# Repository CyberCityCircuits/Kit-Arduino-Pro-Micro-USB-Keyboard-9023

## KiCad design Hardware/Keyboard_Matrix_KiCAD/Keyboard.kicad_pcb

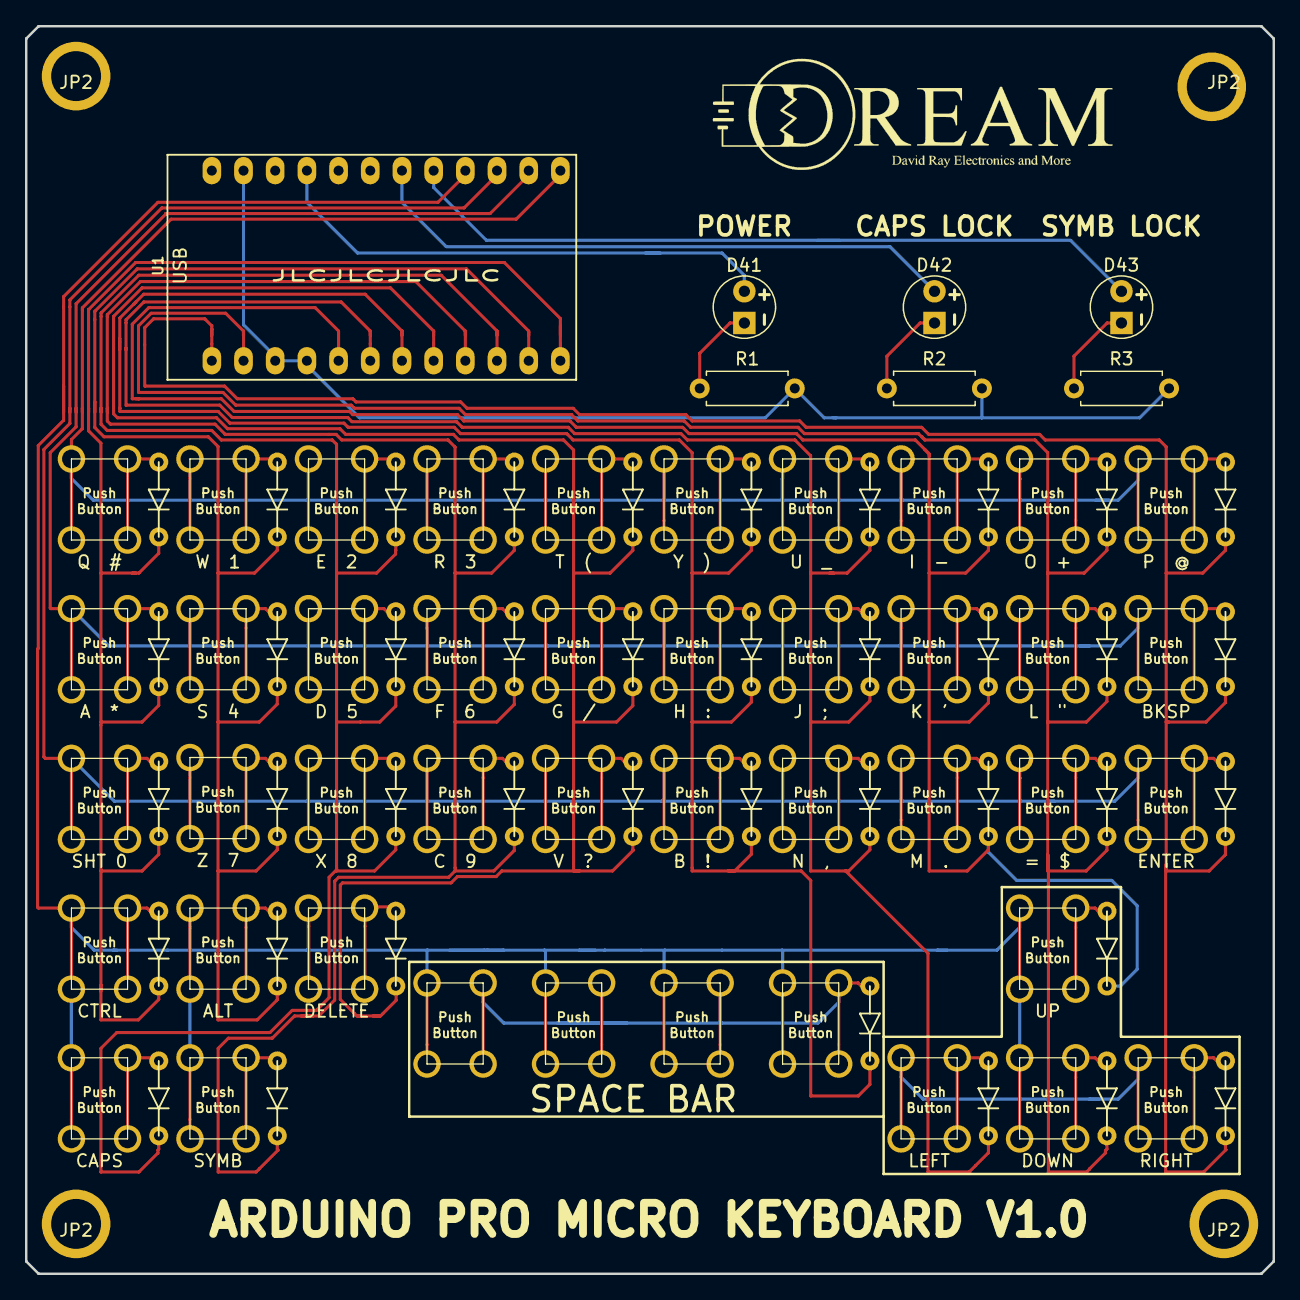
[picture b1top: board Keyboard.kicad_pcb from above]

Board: 2 copper layers, 100.0 x 100.0 mm, 94 parts (0 on the bottom side), 61 nets.

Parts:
=  $: SW_Push; Kailanda Push Button 6.5x4.5_002
A  *: SW_Push; Kailanda Push Button 6.5x4.5_002
ALT: SW_Push; Kailanda Push Button 6.5x4.5_002
B  !: SW_Push; Kailanda Push Button 6.5x4.5_002
BKSP: SW_Push; Kailanda Push Button 6.5x4.5_002
C  9: SW_Push; Kailanda Push Button 6.5x4.5_002
CAPS: SW_Push; Kailanda Push Button 6.5x4.5_002
CTRL: SW_Push; Kailanda Push Button 6.5x4.5_002
D1, D2, D3, D4, D5, D6, D7, D8, D9, D10, D11, D12, D13, D14, D15, D16, D17, D18, D19, D20, D21, D22, D23, D24, D25, D26, D27, D28, D29, D30, D31, D32, D33, D34, D35, D36, D37, D38, D39, D40: 1N4148; DIODE_P6_03kicad_mod
D41, D42, D43: LED; LED_D5.0mm_05
D  5: SW_Push; Kailanda Push Button 6.5x4.5_002
DELETE: SW_Push; Kailanda Push Button 6.5x4.5_002
DOWN: SW_Push; Kailanda Push Button 6.5x4.5_002
E  2: SW_Push; Kailanda Push Button 6.5x4.5_002
ENTER: SW_Push; Kailanda Push Button 6.5x4.5_002
F  6: SW_Push; Kailanda Push Button 6.5x4.5_002
G  /: SW_Push; Kailanda Push Button 6.5x4.5_002
H  :: SW_Push; Kailanda Push Button 6.5x4.5_002
I  -: SW_Push; Kailanda Push Button 6.5x4.5_002
J  ;: SW_Push; Kailanda Push Button 6.5x4.5_002
JP2, JP2#2, JP2#3, JP2#4: 2mm_Hole; 4mm_Mount_Hole
K  ': SW_Push; Kailanda Push Button 6.5x4.5_002
L  ": SW_Push; Kailanda Push Button 6.5x4.5_002
LEFT: SW_Push; Kailanda Push Button 6.5x4.5_002
M  .: SW_Push; Kailanda Push Button 6.5x4.5_002
N  ,: SW_Push; Kailanda Push Button 6.5x4.5_002
O  +: SW_Push; Kailanda Push Button 6.5x4.5_002
P  @: SW_Push; Kailanda Push Button 6.5x4.5_002
Q  #: SW_Push; Kailanda Push Button 6.5x4.5_002
R1, R2, R3: 1000; R_Axial_DIN0207_L6.3mm_D2.5mm_P7.62mm_Horizontal
R  3: SW_Push; Kailanda Push Button 6.5x4.5_002
RIGHT: SW_Push; Kailanda Push Button 6.5x4.5_002
S  4: SW_Push; Kailanda Push Button 6.5x4.5_002
SHT 0: SW_Push; Kailanda Push Button 6.5x4.5_002
SPACE: SW_Push; Kailanda Push Button 6.5x4.5_002
SPACE#2, SPACE#3, SPACE#4: SW_Push; Kailanda Push Button 6.5x4.5_002
SYMB: SW_Push; Kailanda Push Button 6.5x4.5_002
T  (: SW_Push; Kailanda Push Button 6.5x4.5_002
U1: ArduinoProMicro; Arduino_Pro_Micro
U  _: SW_Push; Kailanda Push Button 6.5x4.5_002
UP: SW_Push; Kailanda Push Button 6.5x4.5_002
V  ?: SW_Push; Kailanda Push Button 6.5x4.5_002
W  1: SW_Push; Kailanda Push Button 6.5x4.5_002
X  8: SW_Push; Kailanda Push Button 6.5x4.5_002
Y  ): SW_Push; Kailanda Push Button 6.5x4.5_002
Z  7: SW_Push; Kailanda Push Button 6.5x4.5_002

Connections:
A0: D43.2, U1.17
A1: D42.2, U1.18
COL1: D1.K, D11.K, D21.K, D31.K, U1.12
COL2: D2.K, D12.K, D22.K, D32.K, U1.11
COL3: D3.K, D13.K, D23.K, D33.K, U1.10
COL4: D4.K, D14.K, D24.K, D34.K, U1.9
COL5: D5.K, D15.K, D25.K, D35.K, U1.8
COL6: D6.K, D16.K, D26.K, D36.K, U1.7
COL7: D7.K, D17.K, D27.K, D37.K, U1.6
COL8: D8.K, D18.K, D28.K, D38.K, U1.5
COL9: D9.K, D19.K, D29.K, D39.K, U1.2
COL10: D10.K, D20.K, D30.K, D40.K, U1.1
GND: R1.2, R2.2, R3.2, U1.3, U1.4, U1.23
unnamed: D1.A, Q #.2
unnamed: D2.A, W 1.2
unnamed: D3.A, E 2.2
unnamed: D4.A, R 3.2
unnamed: D5.A, T (.2
unnamed: D6.A, Y ).2
unnamed: D7.A, U _.2
unnamed: D8.A, I -.2
unnamed: D9.A, O +.2
unnamed: D10.A, P @.2
unnamed: A *.2, D11.A
unnamed: D12.A, S 4.2
unnamed: D13.A, D 5.2
unnamed: D14.A, F 6.2
unnamed: D15.A, G /.2
unnamed: D16.A, H :.2
unnamed: D17.A, J ;.2
unnamed: D18.A, K '.2
unnamed: D19.A, L ".2
unnamed: BKSP.2, D20.A
unnamed: D21.A, SHT 0.2
unnamed: D22.A, Z 7.2
unnamed: D23.A, X 8.2
unnamed: C 9.2, D24.A
unnamed: D25.A, V ?.2
unnamed: B !.2, D26.A
unnamed: D27.A, N ,.2
unnamed: D28.A, M ..2
unnamed: = $.2, D29.A
unnamed: D30.A, ENTER.2
unnamed: CTRL.2, D31.A
unnamed: ALT.2, D32.A
unnamed: CAPS.2, D33.A
unnamed: D34.A, SYMB.2
unnamed: D35.A, DELETE.2
unnamed: D36.A, SPACE.2, SPACE#2.2, SPACE#3.2, SPACE#4.2
unnamed: D37.A, LEFT.2
unnamed: D38.A, UP.2
unnamed: D39.A, DOWN.2
unnamed: D40.A, RIGHT.2
unnamed: D41.1, R1.1
unnamed: D42.1, R2.1
unnamed: D43.1, R3.1
POWER: D41.2, U1.21
ROW1: E 2.1, I -.1, O +.1, P @.1, Q #.1, R 3.1, T (.1, U1.13, U _.1, W 1.1, Y ).1
ROW2: A *.1, BKSP.1, D 5.1, F 6.1, G /.1, H :.1, J ;.1, K '.1, L ".1, S 4.1, U1.14
ROW3: = $.1, B !.1, C 9.1, ENTER.1, M ..1, N ,.1, SHT 0.1, U1.15, V ?.1, X 8.1, Z 7.1
ROW4: ALT.1, CAPS.1, CTRL.1, DELETE.1, DOWN.1, LEFT.1, RIGHT.1, SPACE.1, SPACE#2.1, SPACE#3.1, SPACE#4.1, SYMB.1, U1.16, UP.1

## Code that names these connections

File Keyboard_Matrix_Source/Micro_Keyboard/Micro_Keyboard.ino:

//****************************************************
//This is for the Keyboard Matrix for sale
//on Tindie.com from David Ray Electronics and More.
//This is built around the Arduino Pro Micro.
//Use this any way you see fit.
//www.DREAM-Enterprise.com
//****************************************************

#include <Keypad.h>
#include <Keyboard.h>

int CAPS_LED = 19;
int SYMB_LED = 18;

int CAPSLOCK = 0;
int SYMBLOCK = 0;

const byte ROWS = 4;
const byte COLS = 10;

byte rowPins[ROWS] = {10, 16, 14, 15}; //connect to the row pinouts of the keypad
byte colPins[COLS] = {9, 8, 7, 6, 5, 4, 3, 2, 1, 0}; //connect to the column pinouts of the keypad

//KEY LAYOUT
//           COL1  COL2  COL3  COL4  COL5  COL6  COL7  COL8  COL9  COL10
//           PIN9  PIN8  PIN7  PIN6  PIN5  PIN4  PIN3  PIN2  PIN1  PIN0
//ROW1 PIN10 Q     W     E     R     T     Y     U     I     P     O
//ROW2 PIN16 A     S     D     F     G     H     J     K     bck   L
//ROW3 PIN14 shf   Z     X     C     V     B     N     M     ent   =
//ROW4 PIN15 ctrl  alt   caps  symb  del   spc   left  up    down  right

//SYMBOL LAYOUT
//           COL1  COL2  COL3  COL4  COL5  COL6  COL7  COL8  COL9  COL10
//           PIN9  PIN8  PIN7  PIN6  PIN5  PIN4  PIN3  PIN2  PIN1  PIN0
//ROW1 PIN10 #     1     2     3     (     )     _     -     @     +
//ROW2 PIN16 *     4     5     6     /     :     ;     '     bck   "
//ROW3 PIN14 0     7     8     9     ?     !     ,     .     ent   $
//ROW4 PIN15 ctrl  alt   caps  symb  del   spc   left  up    down  right

byte keys[ROWS][COLS] = {
  { 1, 2, 3, 4, 5, 6, 7, 8, 9, 10},
  {11, 12, 13, 14, 15, 16, 17, 18, 19, 20},
  {21, 22, 23, 24, 25, 26, 27, 28, 29, 30},
  {31, 32, 33, 34, 35, 36, 37, 38, 39, 40}
};

Keypad keypad = Keypad( makeKeymap(keys), rowPins, colPins, ROWS, COLS );

void setup() {

  Serial.begin(9600);
  pinMode(CAPS_LED, OUTPUT);
  pinMode(SYMB_LED, OUTPUT);

  digitalWrite (CAPS_LED, HIGH); digitalWrite (SYMB_LED, HIGH); delay(250);
  digitalWrite (CAPS_LED, LOW); digitalWrite (SYMB_LED, LOW); delay(250);

  digitalWrite (CAPS_LED, HIGH); digitalWrite (SYMB_LED, HIGH); delay(250);
  digitalWrite (CAPS_LED, LOW); digitalWrite (SYMB_LED, LOW); delay(250);

  digitalWrite (CAPS_LED, HIGH); digitalWrite (SYMB_LED, HIGH); delay(250);
  digitalWrite (CAPS_LED, LOW); digitalWrite (SYMB_LED, LOW); delay(250);

  Keyboard.begin();

}

void loop() {
  
  if (CAPSLOCK == 1){digitalWrite(CAPS_LED, HIGH);
  } else{digitalWrite(CAPS_LED,LOW);}

  if (SYMBLOCK == 1){digitalWrite(SYMB_LED, HIGH);
  } else{digitalWrite(SYMB_LED,LOW);}
 
  char key = keypad.getKey();

  if (key != NO_KEY) {

    if (key ==  1) {if (SYMBLOCK == 1){Keyboard.write('#');}else{Keyboard.write('q');}}
    if (key ==  2) {if (SYMBLOCK == 1){Keyboard.write('1');}else{Keyboard.write('w');}}
    if (key ==  3) {if (SYMBLOCK == 1){Keyboard.write('2');}else{Keyboard.write('e');}}
    if (key ==  4) {if (SYMBLOCK == 1){Keyboard.write('3');}else{Keyboard.write('r');}}
    if (key ==  5) {if (SYMBLOCK == 1){Keyboard.write('(');}else{Keyboard.write('t');}}
    if (key ==  6) {if (SYMBLOCK == 1){Keyboard.write(')');}else{Keyboard.write('y');}}
    if (key ==  7) {if (SYMBLOCK == 1){Keyboard.write('_');}else{Keyboard.write('u');}}
    if (key ==  8) {if (SYMBLOCK == 1){Keyboard.write('-');}else{Keyboard.write('i');}}
    if (key ==  9) {if (SYMBLOCK == 1){Keyboard.write('@');}else{Keyboard.write('p');}}
    if (key == 10) {if (SYMBLOCK == 1){Keyboard.write('+');}else{Keyboard.write('o');}}
    
    if (key == 11) {if (SYMBLOCK == 1){Keyboard.write('*');}else{Keyboard.write('a');}}
    if (key == 12) {if (SYMBLOCK == 1){Keyboard.write('4');}else{Keyboard.write('s');}}
    if (key == 13) {if (SYMBLOCK == 1){Keyboard.write('5');}else{Keyboard.write('d');}}
    if (key == 14) {if (SYMBLOCK == 1){Keyboard.write('6');}else{Keyboard.write('f');}}
    if (key == 15) {if (SYMBLOCK == 1){Keyboard.write('/');}else{Keyboard.write('g');}}
    if (key == 16) {if (SYMBLOCK == 1){Keyboard.write(':');}else{Keyboard.write('h');}}
    if (key == 17) {if (SYMBLOCK == 1){Keyboard.write(';');}else{Keyboard.write('j');}}
    if (key == 18) {if (SYMBLOCK == 1){Keyboard.write("'");}else{Keyboard.write('k');}}
    if (key == 19) {
      Keyboard.press(KEY_BACKSPACE); //backspace
      Keyboard.release(KEY_BACKSPACE); //backspace
    }
    if (key == 20) {if (SYMBLOCK == 1){Keyboard.write('"');}else{Keyboard.write('l');}}
    
    if (key == 21) {if (SYMBLOCK == 1){Keyboard.write('0');}else{
      Keyboard.press(KEY_LEFT_SHIFT); Keyboard.release(KEY_LEFT_SHIFT);}}
    if (key == 22) {if (SYMBLOCK == 1){Keyboard.write('7');}else{Keyboard.write('z');}}
    if (key == 23) {if (SYMBLOCK == 1){Keyboard.write('8');}else{Keyboard.write('x');}}
    if (key == 24) {if (SYMBLOCK == 1){Keyboard.write('9');}else{Keyboard.write('c');}}
    if (key == 25) {if (SYMBLOCK == 1){Keyboard.write('?');}else{Keyboard.write('v');}}
    if (key == 26) {if (SYMBLOCK == 1){Keyboard.write('!');}else{Keyboard.write('b');}}
    if (key == 27) {if (SYMBLOCK == 1){Keyboard.write(',');}else{Keyboard.write('n');}}
    if (key == 28) {if (SYMBLOCK == 1){Keyboard.write('.');}else{Keyboard.write('m');}}
    if (key == 29) {Keyboard.press(KEY_RETURN);Keyboard.release(KEY_RETURN);}
    if (key == 30) {if (SYMBLOCK == 1){Keyboard.write('$');}else{Keyboard.write('=');}}
    
    if (key == 31) {Keyboard.write(KEY_LEFT_CTRL); Keyboard.release(KEY_LEFT_CTRL);}
    if (key == 32) {Keyboard.write(KEY_LEFT_ALT);Keyboard.release(KEY_LEFT_ALT);}
    if (key == 33) {if (CAPSLOCK == 0){CAPSLOCK = 1;}else{CAPSLOCK = 0;}
                    Keyboard.press(KEY_CAPS_LOCK);Keyboard.release(KEY_CAPS_LOCK);}
    if (key == 34) {if (SYMBLOCK == 0){SYMBLOCK = 1;}else{SYMBLOCK = 0;}}
    if (key == 35) {Keyboard.press(KEY_DELETE); Keyboard.release(KEY_DELETE);}
    if (key == 36) {Keyboard.write(' ');}
    if (key == 37) {Keyboard.press(KEY_LEFT_ARROW); Keyboard.release(KEY_LEFT_ARROW);}
    if (key == 38) {Keyboard.press(KEY_UP_ARROW); Keyboard.release(KEY_UP_ARROW);}
    if (key == 39) {Keyboard.press(KEY_RIGHT_ARROW); Keyboard.release(KEY_RIGHT_ARROW);}
    if (key == 40) {Keyboard.press(KEY_DOWN_ARROW); Keyboard.release(KEY_DOWN_ARROW);}
  }
}

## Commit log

2019-03-24 Initial Commit
    Uploading Arduino Sketch and Kicad Design Files.
2019-03-24 Pictures
    Uploaded Pictures
2020-10-14 Updated for Cyber Box Kit
